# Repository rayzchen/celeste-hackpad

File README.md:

# Celeste Hackpad
8-key macropad with ZXC, Esc, arrow keys. Features LEDs, OLED and rotary encoder.

## Schematic

## PCB

## CAD assembly

## BOM
- 8x Cherry MX Switches
- 8x DSA Keycaps
- 9x Through-hole 1N4148 DO-35 Diodes
- 8x SK6812 MINI-E LEDs
- 1x 0.91" 128x32 OLED Display
- 1x EC11 Rotary Encoder
- 1x XIAO RP2040
- 1x Case

## Controls
To aid speedrunning Celeste, many key chords have been implemented.
- Esc + Down arrow: F (bound to menu down and menu confirm)
- Arrow keys + Esc: S (bound to crouch dash)
- C + Up arrow: D (bound to second jump button)
- Esc + Up arrow: Toggle LEDs
- Esc + Left arrow: Alt+Tab
- Z + Esc: Tab (bound to journal)

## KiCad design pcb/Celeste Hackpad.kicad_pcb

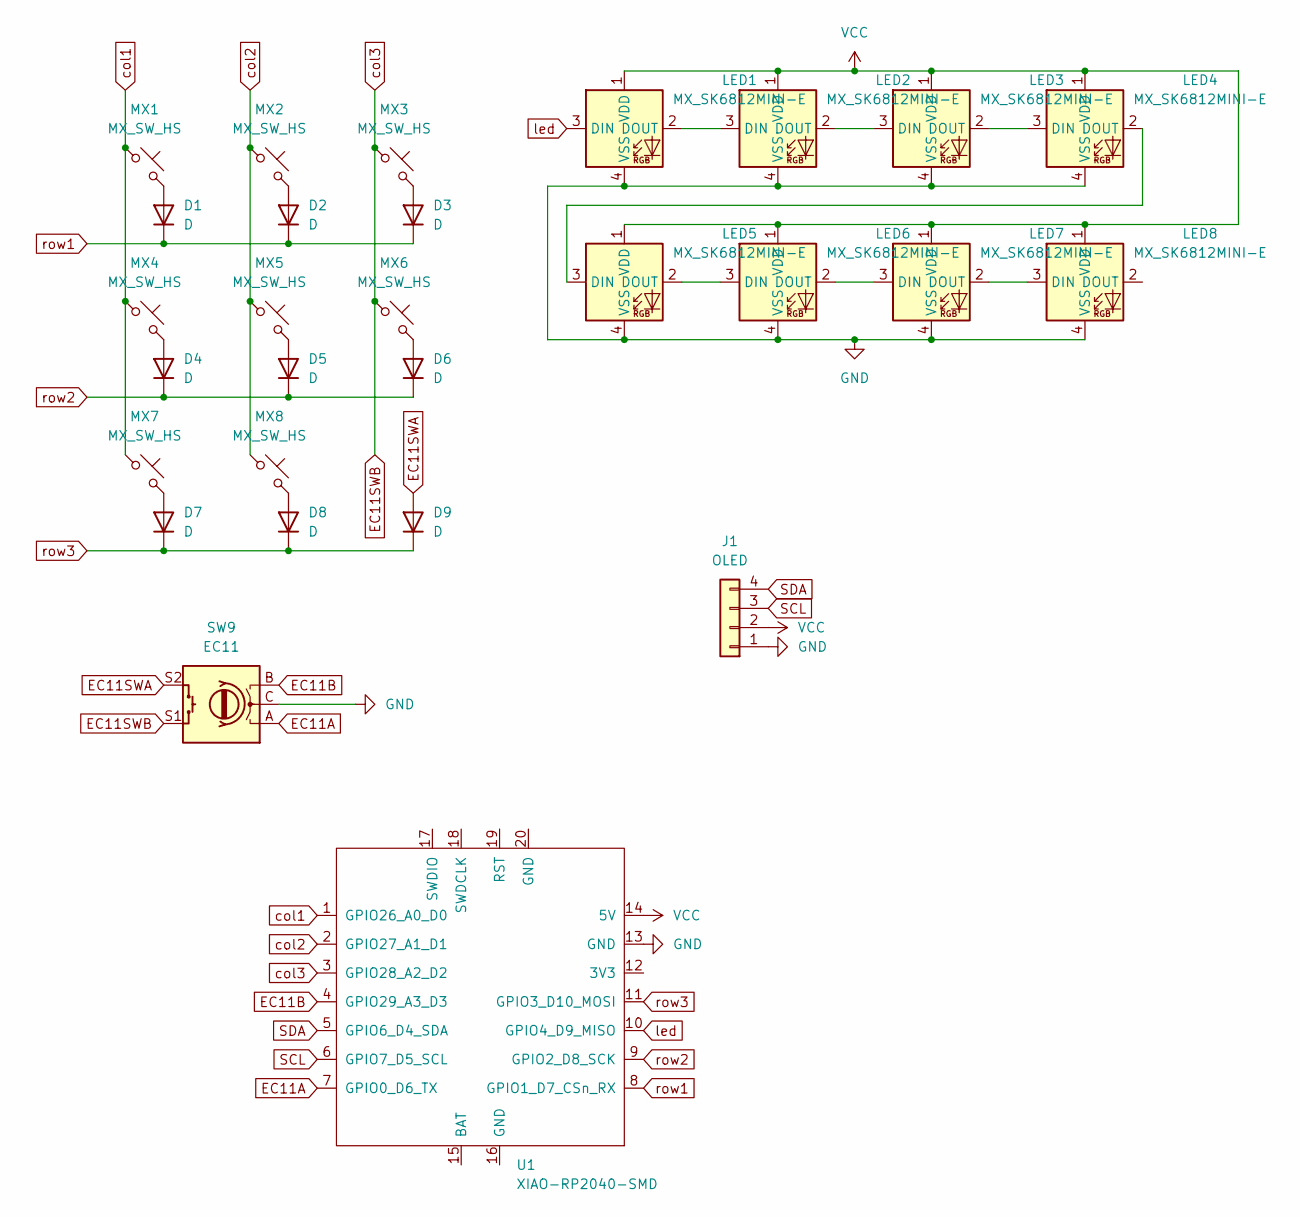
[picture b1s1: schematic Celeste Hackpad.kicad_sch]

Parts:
D1, D2, D3, D4, D5, D6, D7, D8, D9: D; D_DO-35_SOD27_P7.62mm_Horizontal
J1: OLED; SSD1306-0.91-OLED-4pin-128x32
LED1, LED2, LED3, LED4, LED5, LED6, LED7, LED8: MX_SK6812MINI-E; LED_MX_6028R
MX1, MX2, MX3, MX4, MX5, MX6, MX7, MX8: MX_SW_HS; SW_Cherry_MX_1.00u_PCB
SW9: EC11; RotaryEncoder_Alps_EC11E-Switch_Vertical_H20mm
U1: XIAO-RP2040-SMD

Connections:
EC11A: SW9.A, U1.7 (GPIO0_D6_TX)
EC11B: SW9.B, U1.4 (GPIO29_A3_D3)
EC11SWA: D9.2 (A), SW9.S2
EC11SWB: MX3.1, MX6.1, SW9.S1, U1.3 (GPIO28_A2_D2)
GND: J1.1, LED1.4 (VSS), LED2.4 (VSS), LED3.4 (VSS), LED4.4 (VSS), LED5.4 (VSS), LED6.4 (VSS), LED7.4 (VSS), LED8.4 (VSS), SW9.C, U1.13 (GND)
unnamed: D1.2 (A), MX1.2
unnamed: D2.2 (A), MX2.2
unnamed: D3.2 (A), MX3.2
unnamed: D4.2 (A), MX4.2
unnamed: D5.2 (A), MX5.2
unnamed: D6.2 (A), MX6.2
unnamed: D7.2 (A), MX7.2
unnamed: D8.2 (A), MX8.2
unnamed: LED1.2 (DOUT), LED2.3 (DIN)
unnamed: LED2.2 (DOUT), LED3.3 (DIN)
unnamed: LED3.2 (DOUT), LED4.3 (DIN)
unnamed: LED4.2 (DOUT), LED5.3 (DIN)
unnamed: LED5.2 (DOUT), LED6.3 (DIN)
unnamed: LED6.2 (DOUT), LED7.3 (DIN)
unnamed: LED7.2 (DOUT), LED8.3 (DIN)
SCL: J1.3, U1.6 (GPIO7_D5_SCL)
SDA: J1.4, U1.5 (GPIO6_D4_SDA)
VCC: J1.2, LED1.1 (VDD), LED2.1 (VDD), LED3.1 (VDD), LED4.1 (VDD), LED5.1 (VDD), LED6.1 (VDD), LED7.1 (VDD), LED8.1 (VDD), U1.14 (5V)
col1: MX1.1, MX4.1, MX7.1, U1.1 (GPIO26_A0_D0)
col2: MX2.1, MX5.1, MX8.1, U1.2 (GPIO27_A1_D1)
led: LED1.3 (DIN), U1.10 (GPIO4_D9_MISO)
row1: D1.1 (K), D2.1 (K), D3.1 (K), U1.8 (GPIO1_D7_CSn_RX)
row2: D4.1 (K), D5.1 (K), D6.1 (K), U1.9 (GPIO2_D8_SCK)
row3: D7.1 (K), D8.1 (K), D9.1 (K), U1.11 (GPIO3_D10_MOSI)

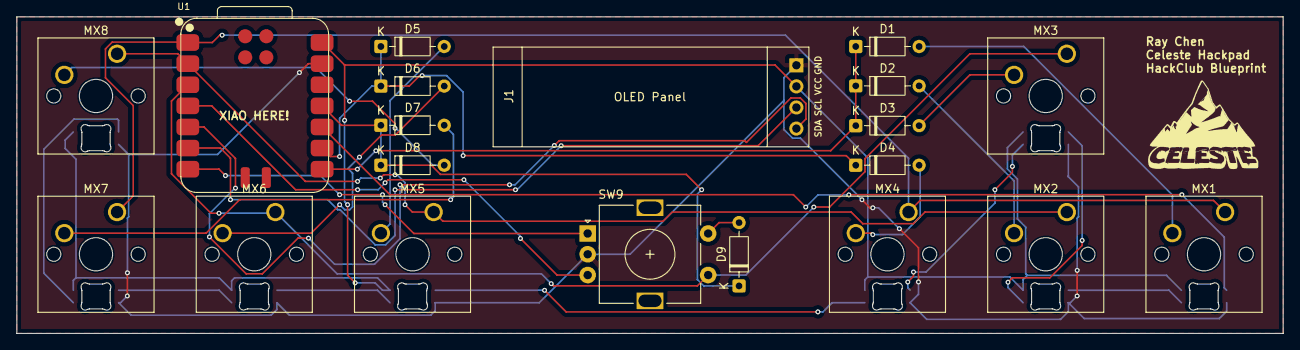
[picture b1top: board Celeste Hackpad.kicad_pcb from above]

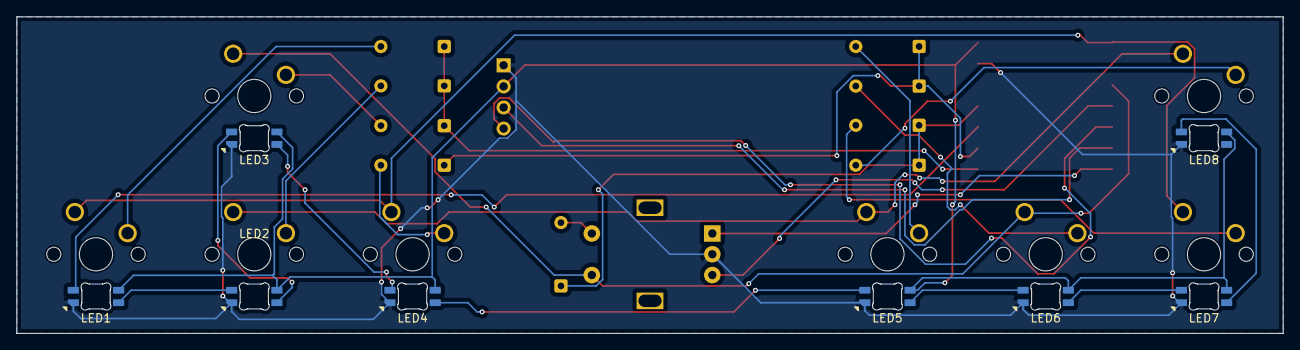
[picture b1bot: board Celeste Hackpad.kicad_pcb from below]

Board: 2 copper layers, 152.4 x 38.1 mm, 28 parts (8 on the bottom side), 29 nets.

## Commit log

2025-11-30 Redraw tracks by hand
2025-12-01 Shrink size of pcb
2025-12-01 Clean up root directory
2025-12-01 Write basic key matrix firmware
2025-12-01 Add ground fill
2025-12-01 Add README
2025-12-01 Reset offset of LED
2025-12-03 Finish case design
2026-01-11 Add RGB neopixel support
2026-01-12 Fix tolerances on case
2026-01-12 Raise OLED above plate
2026-01-15 Implement key chording sequences
2026-01-21 Increased tolerance remodel
2026-01-21 Add AltTab and Tab chords
2026-01-21 Add keybinds to readme
2026-01-21 Update case image
2026-02-05 Three custom OLED GUI screens
